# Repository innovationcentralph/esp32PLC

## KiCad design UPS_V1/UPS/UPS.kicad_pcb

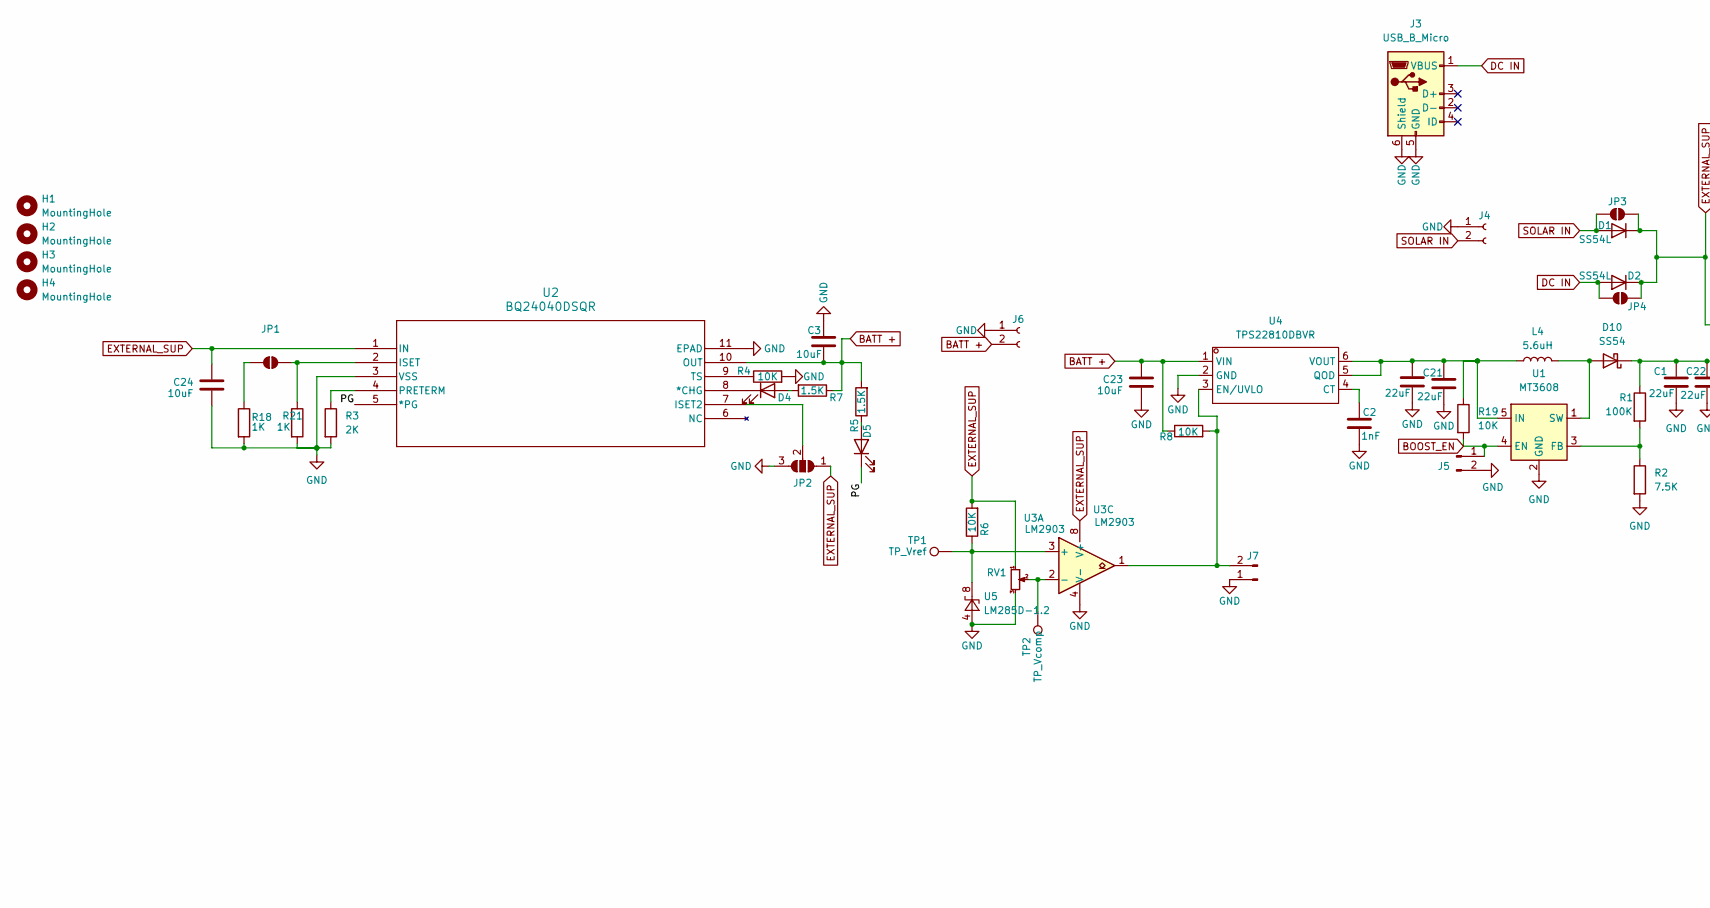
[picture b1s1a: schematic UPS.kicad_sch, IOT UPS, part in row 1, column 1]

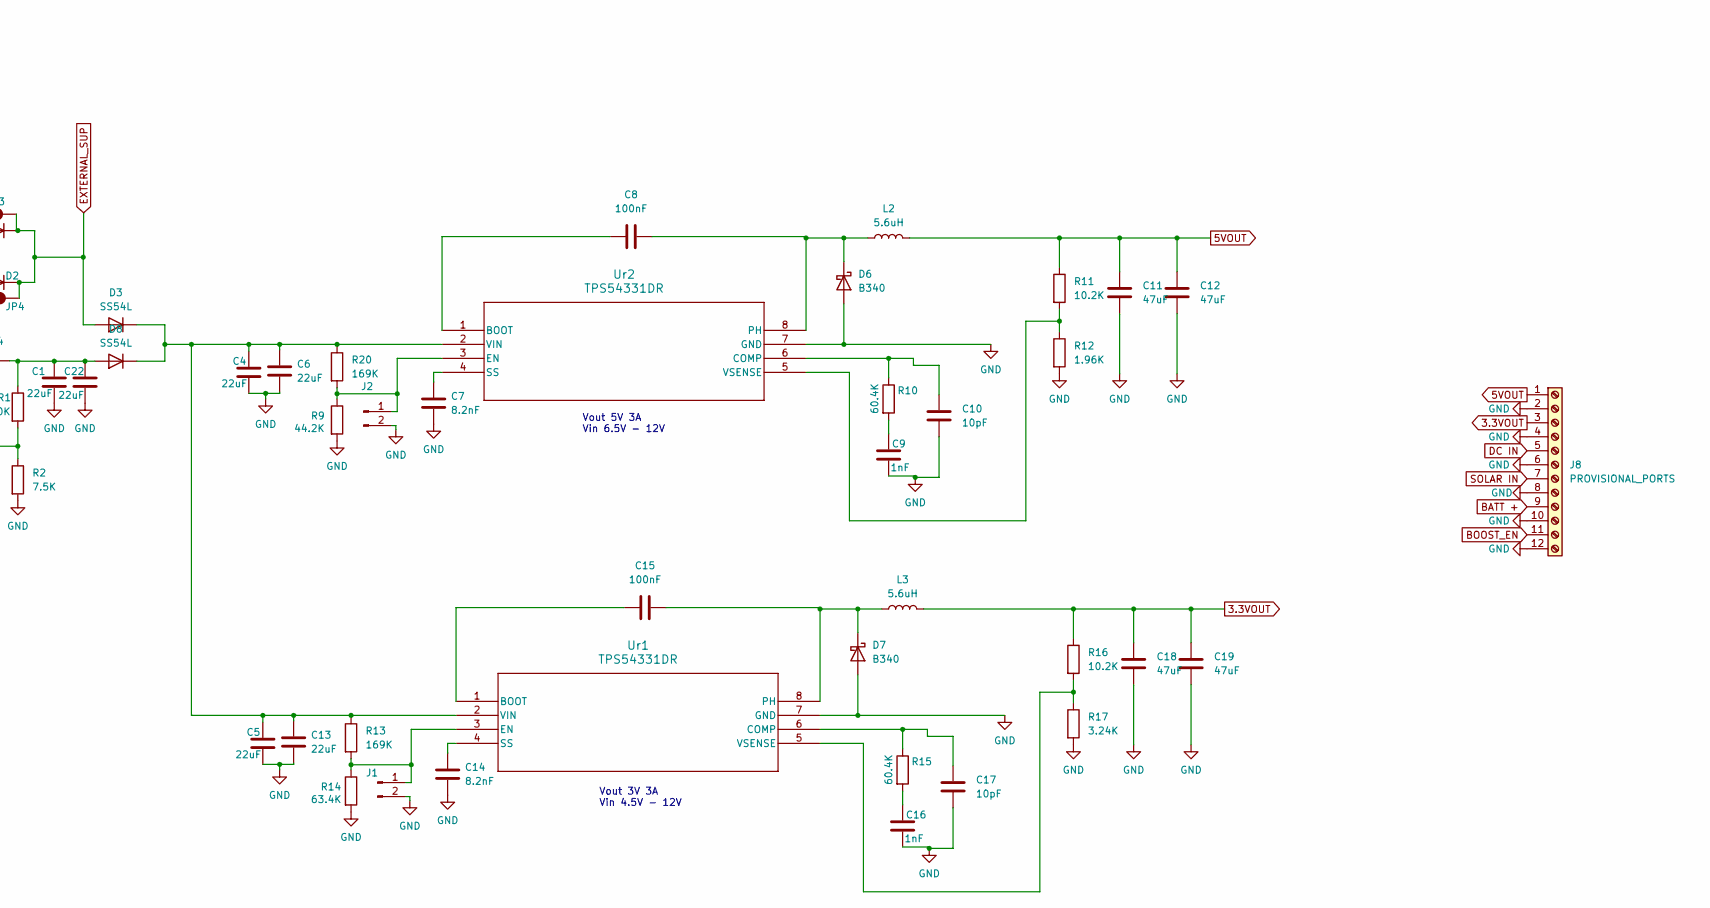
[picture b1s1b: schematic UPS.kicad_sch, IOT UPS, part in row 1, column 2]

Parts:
C1, C4, C5, C6, C13, C20, C21, C22: 22uF; C_0805_2012Metric_Pad1.18x1.45mm_HandSolder; LCSC C45783
C2, C9, C16: 1nF; C_0603_1608Metric_Pad1.08x0.95mm_HandSolder; LCSC C100040
C3, C23, C24: 10uF; C_0805_2012Metric_Pad1.18x1.45mm_HandSolder; LCSC C15850
C7, C14: 8.2nF; C_0603_1608Metric_Pad1.08x0.95mm_HandSolder; LCSC C1322360
C8, C15: 100nF; C_0603_1608Metric_Pad1.08x0.95mm_HandSolder; LCSC C14663
C10, C17: 10pF; C_0603_1608Metric_Pad1.08x0.95mm_HandSolder; LCSC C1634
C11, C12, C18, C19: 47uF; C_1210_3225Metric_Pad1.33x2.70mm_HandSolder; LCSC C77101
D1, D2, D3, D8: SS54L; D_SMB_Handsoldering; LCSC C432138
D4: CHG; LED_0805_2012Metric_Pad1.15x1.40mm_HandSolder; LCSC C2286
D5: PGOOD; LED_0805_2012Metric_Pad1.15x1.40mm_HandSolder; LCSC C2297
D6, D7: B340; D_SMA_Handsoldering; LCSC C17101
D10: SS54; D_SMA_Handsoldering; LCSC C22452
H1, H2, H3, H4: MountingHole; MountingHole_3.2mm_M3
J1, J2, J5, J7: Conn_01x02_Pin; PinHeader_1x02_P2.54mm_Vertical
J3: USB_B_Micro; USB_Micro-B_Molex-105017-0001; LCSC C404969
J4, J6: Conn_01x02_Socket; JST_EH_S2B-EH_1x02_P2.50mm_Horizontal
J8: PROVISIONAL_PORTS; TerminalBlock_Xinya_XY308-2.54-12P_1x12_P2.54mm_Horizontal
JP1, JP3, JP4: SolderJumper_2_Open; SolderJumper-2_P1.3mm_Open_RoundedPad1.0x1.5mm
JP2: SolderJumper_3_Open; SolderJumper-3_P1.3mm_Open_RoundedPad1.0x1.5mm
L2, L3, L4: 5.6uH; L_Sunlord_MWSA0603S; LCSC C408448
R1: 100K; R_0603_1608Metric_Pad0.98x0.95mm_HandSolder; LCSC C25803
R2: 7.5K; R_0603_1608Metric_Pad0.98x0.95mm_HandSolder; LCSC C23234
R3: 2K; R_0603_1608Metric_Pad0.98x0.95mm_HandSolder; LCSC C22975
R4, R6, R8, R19: 10K; R_0603_1608Metric_Pad0.98x0.95mm_HandSolder; LCSC C25804
R5, R7: 1.5K; R_0603_1608Metric_Pad0.98x0.95mm_HandSolder; LCSC C22843
R9: 44.2K; R_0603_1608Metric_Pad0.98x0.95mm_HandSolder; LCSC C23056
R10, R15: 60.4K; R_0603_1608Metric_Pad0.98x0.95mm_HandSolder; LCSC C2933245
R11, R16: 10.2K; R_0603_1608Metric_Pad0.98x0.95mm_HandSolder; LCSC C22772
R12: 1.96K; R_0603_1608Metric_Pad0.98x0.95mm_HandSolder; LCSC C22854
R13, R20: 169K; R_0603_1608Metric_Pad0.98x0.95mm_HandSolder; LCSC C22817
R14: 63.4K; R_0603_1608Metric_Pad0.98x0.95mm_HandSolder; LCSC C23093
R17: 3.24K; R_0603_1608Metric_Pad0.98x0.95mm_HandSolder; LCSC C22994
R18, R21: 1K; R_0603_1608Metric_Pad0.98x0.95mm_HandSolder; LCSC C21190
RV1: R_Potentiometer_Small; 3296W-1-103_BRN; LCSC C118954
TP1: TP_Vref; TestPoint_Keystone_5005-5009_Compact
TP2: TP_Vcomp; TestPoint_Keystone_5005-5009_Compact
U1: MT3608; SOT-23-6; LCSC C19189893
U2: BQ24040DSQR; DSQ10_P9X1P5; LCSC C81080
U3: LM2903; SOIC-8_3.9x4.9mm_P1.27mm; LCSC C7549
U4: TPS22810DBVR; SOT-23-6_L2.9-W1.6-P0.95-LS2.8-BL; LCSC C205990
U5: LM285D-1.2; SOIC-8_3.9x4.9mm_P1.27mm; LCSC C5145309
Ur1, Ur2: TPS54331DR; TPS54331; LCSC C9865

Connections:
3.3VOUT: C18.2, C19.2, J8.3, L3.2, R16.1
5VOUT: C11.2, C12.2, J8.1, L2.2, R11.1
/PG: D5.1 (K), U2.5 (*PG)
BATT +: C3.2, C23.1, J6.2, J8.9, R5.2, R7.1, R8.1, U2.10 (OUT), U4.1 (VIN)
BOOST_EN: J5.1, J8.11, R19.2, U1.4 (EN)
DC IN: D2.2 (A), J3.1 (VBUS), J8.5, JP4.2 (B)
EXTERNAL_SUP: C24.1, D1.1 (K), D2.1 (K), D3.2 (A), JP2.1 (A), JP3.1 (A), JP4.1 (A), R6.2, RV1.1, U2.1 (IN), U3.8 (V+)
GND: C1.2, C2.1, C3.1, C4.2, C5.2, C6.2, C7.2, C9.1, C10.1, C11.1, C12.1, C13.2, C14.2, C16.1, C17.1, C18.1, C19.1, C20.2, C21.2, C22.2, C23.2, C24.2, D6.2 (A), D7.2 (A), J1.2, J2.2, J3.5 (GND), J3.6 (Shield), J4.1, J5.2, J6.1, J7.1, J8.2, J8.4, J8.6, J8.8, J8.10, J8.12, JP2.3 (B), R2.2, R3.2, R4.2, R9.2, R12.2, R14.2, R17.2, R18.2, R21.2, RV1.3, U1.2 (GND), U2.3 (VSS), U2.11 (EPAD), U3.4 (V-), U4.2 (GND), U5.4 (A), Ur1.7 (GND), Ur2.7 (GND)
unnamed: C9.2, R10.2
unnamed: C16.2, R15.2
unnamed: C4.1, C5.1, C6.1, C13.1, D3.1 (K), D8.1 (K), R13.1, R20.1, Ur1.2 (VIN), Ur2.2 (VIN)
unnamed: D4.2 (A), R7.2
unnamed: D4.1 (K), U2.8 (*CHG)
unnamed: D5.2 (A), R5.1
unnamed: C8.2, D6.1 (K), L2.1, Ur2.8 (PH)
unnamed: C15.2, D7.1 (K), L3.1, Ur1.8 (PH)
unnamed: D10.2 (A), L4.2, U1.1 (SW)
unnamed: C1.1, C22.1, D8.2 (A), D10.1 (K), R1.1
unnamed: J1.1, R13.2, R14.1, Ur1.3 (EN)
unnamed: J2.1, R9.1, R20.2, Ur2.3 (EN)
unnamed: J7.2, R8.2, U3.1, U4.3 (EN/UVLO)
unnamed: JP1.1 (A), R21.1, U2.2 (ISET)
unnamed: JP1.2 (B), R18.1
unnamed: JP2.2 (C), U2.7 (ISET2)
unnamed: R1.2, R2.1, U1.3 (FB)
unnamed: C20.1, C21.1, L4.1, R19.1, U1.5 (IN), U4.5 (QOD), U4.6 (VOUT)
unnamed: R3.1, U2.4 (PRETERM)
unnamed: R4.1, U2.9 (TS)
unnamed: R6.1, TP1.1, U3.3 (+), U5.8 (K)
unnamed: RV1.2, TP2.1, U3.2 (-)
unnamed: C2.2, U4.4 (CT)
unnamed: C15.1, Ur1.1 (BOOT)
unnamed: C17.2, R15.1, Ur1.6 (COMP)
unnamed: C14.1, Ur1.4 (SS)
unnamed: R16.2, R17.1, Ur1.5 (VSENSE)
unnamed: C8.1, Ur2.1 (BOOT)
unnamed: C10.2, R10.1, Ur2.6 (COMP)
unnamed: C7.1, Ur2.4 (SS)
unnamed: R11.2, R12.1, Ur2.5 (VSENSE)
SOLAR IN: D1.2 (A), J4.2, J8.7, JP3.2 (B)

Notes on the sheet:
Vout 3V 3A Vin 4.5V - 12V
Vout 5V 3A Vin 6.5V - 12V

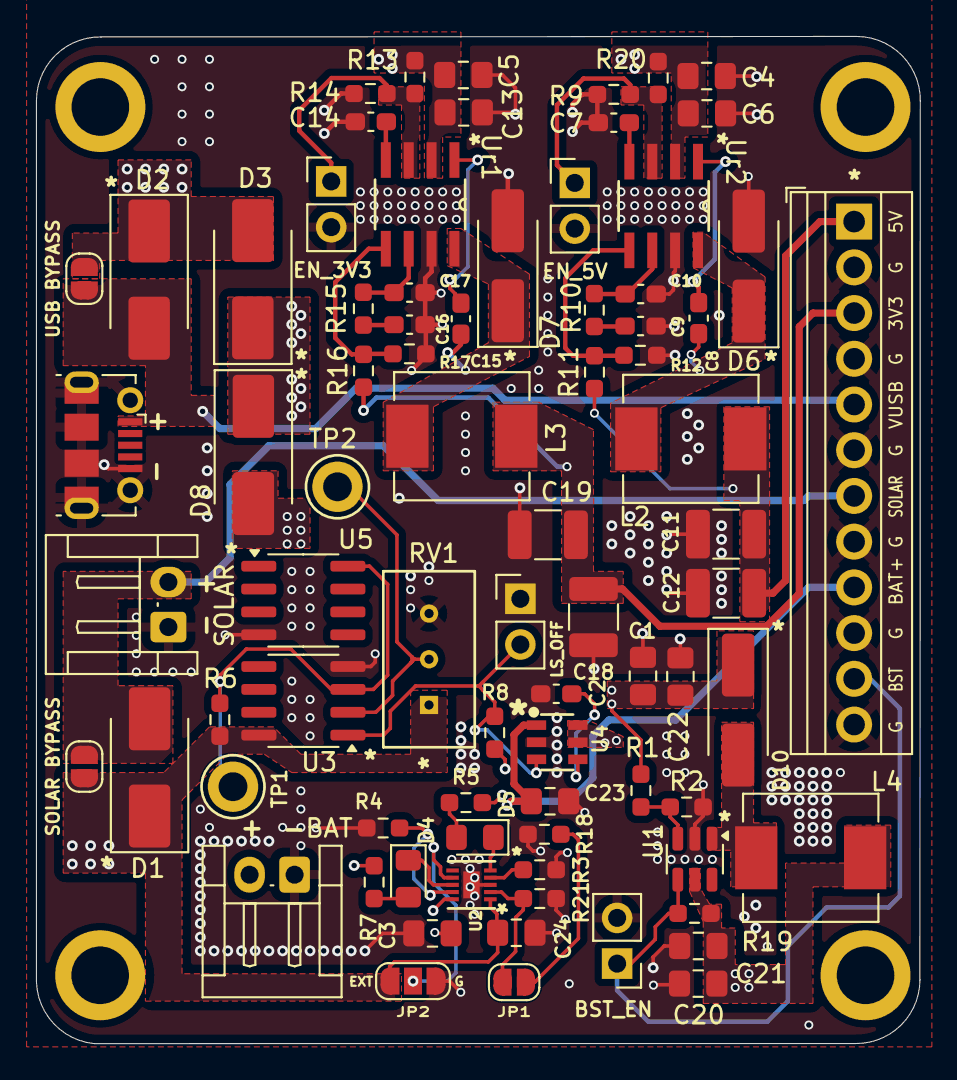
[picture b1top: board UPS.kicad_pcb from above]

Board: 2 copper layers, 49.1 x 56.0 mm, 83 parts (0 on the bottom side), 40 nets.
